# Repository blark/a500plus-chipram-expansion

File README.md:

# a500plus-chipram-expansion

This is a 1MB chip RAM expansion designed for the Amiga 500+ in KiCad.

It is in the experimental phase, but I've assembled it and it appears to be working great. However, you've been warned!

## Features

Small (42mmx52mm), simple design using only a 40 pin (2x20) female 2.54mm connector. The remaining pins are for the RTC which is on-board the A500+, so they are unecessary for RAM expansion. This makes it possible to use a 40 pin connector, which is cheaper and easier to find.

WARNING: **make sure you plug it in correctly** see the [install section](https://github.com/blark/a500plus-chipram-expansion#install) below.

## Schematic

A PDF file of the schematic can be found [in this repo](https://raw.githubusercontent.com/blark/a500plus-chipram-expansion/master/media/schematic.pdf).

## Ordering

I shared the design at [Oshpark](https://oshpark.com/shared_projects/eQQuG4Mi)

## BOM
| Designator | Description |
| ---------- | ----------- |
| J1 | 40P (20x2) female header 2.54mm |
| J2 | 1x DPDT Sub-Miniature Slide switch (9x4x3.5mm, easily found on Ebay) |
| U1-U2 | IS41C16257-35T 4mbit DRAM (256 x 16) |
| C1-C6 | 100nF 603 SMD capacitor |
| C7 | 10uF 805 SMD capacitor |
| R1 | 10K 805 SMD resistor |

## Install

Be careful during install to match pin 1 on the expansion with pin 1 on the A500+ memory expansion port! Here's an image of how it should be installed:

## Thanks

The parts library I've included (and expanded upon) in this repo is "borrowed" from [Kai Robinson](https://github.com/kr239) check out his great projects!

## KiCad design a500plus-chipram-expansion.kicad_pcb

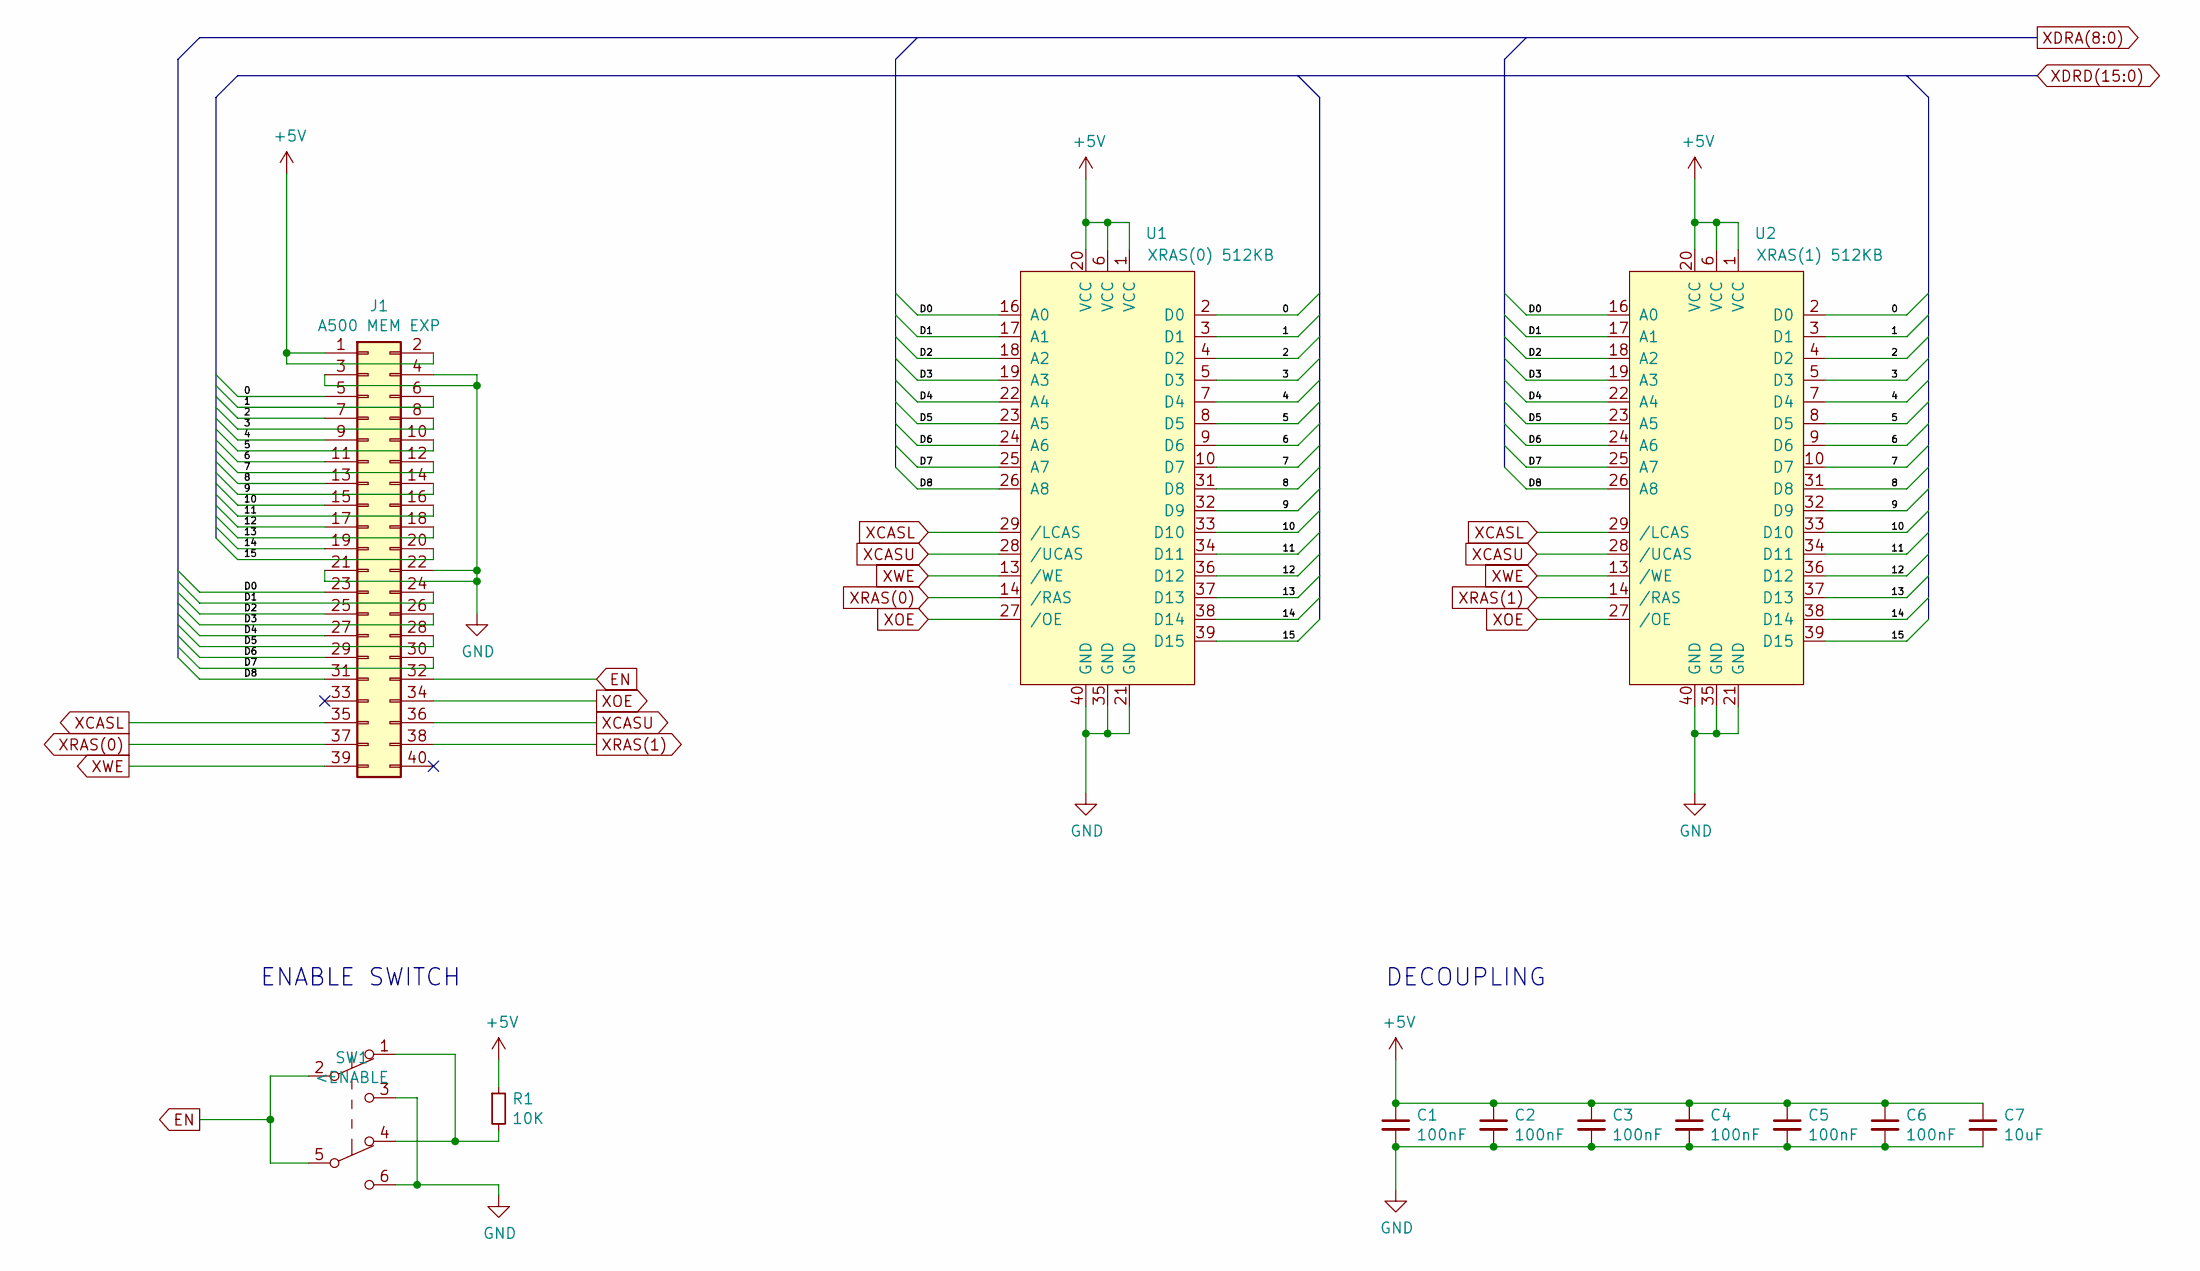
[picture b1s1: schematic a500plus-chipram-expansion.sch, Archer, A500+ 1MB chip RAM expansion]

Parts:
C1, C2, C3, C4, C5, C6: 100nF; C_0603_1608Metric_Pad1.05x0.95mm_HandSolder
C7: 10uF; C_0805_2012Metric_Pad1.15x1.40mm_HandSolder
J1: A500 MEM EXP; PinHeader_2x20_P2.54mm_Horizontal
R1: 10K; R_0805_2012Metric_Pad1.15x1.40mm_HandSolder
SW1: <ENABLE; SW_CuK_JS202011AQN_DPDT_Angled
U1: XRAS(0) 512KB; TSOP-II-40
U2: XRAS(1) 512KB; TSOP-II-40

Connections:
+5V: C1.1, C2.1, C3.1, C4.1, C5.1, C6.1, C7.1, J1.1, J1.2, R1.1, U1.1 (VCC), U1.6 (VCC), U1.20 (VCC), U2.1 (VCC), U2.6 (VCC), U2.20 (VCC)
/0: J1.5, U1.2 (D0), U2.2 (D0)
/1: J1.6, U1.3 (D1), U2.3 (D1)
/2: J1.7, U1.4 (D2), U2.4 (D2)
/3: J1.8, U1.5 (D3), U2.5 (D3)
/4: J1.9, U1.7 (D4), U2.7 (D4)
/5: J1.10, U1.8 (D5), U2.8 (D5)
/6: J1.11, U1.9 (D6), U2.9 (D6)
/7: J1.12, U1.10 (D7), U2.10 (D7)
/8: J1.13, U1.31 (D8), U2.31 (D8)
/9: J1.14, U1.32 (D9), U2.32 (D9)
/10: J1.15, U1.33 (D10), U2.33 (D10)
/11: J1.16, U1.34 (D11), U2.34 (D11)
/12: J1.17, U1.36 (D12), U2.36 (D12)
/13: J1.18, U1.37 (D13), U2.37 (D13)
/14: J1.19, U1.38 (D14), U2.38 (D14)
/15: J1.20, U1.39 (D15), U2.39 (D15)
/D0: J1.23, U1.16 (A0), U2.16 (A0)
/D1: J1.24, U1.17 (A1), U2.17 (A1)
/D2: J1.25, U1.18 (A2), U2.18 (A2)
/D3: J1.26, U1.19 (A3), U2.19 (A3)
/D4: J1.27, U1.22 (A4), U2.22 (A4)
/D5: J1.28, U1.23 (A5), U2.23 (A5)
/D6: J1.29, U1.24 (A6), U2.24 (A6)
/D7: J1.30, U1.25 (A7), U2.25 (A7)
/D8: J1.31, U1.26 (A8), U2.26 (A8)
EN: J1.32, SW1.2 (B), SW1.5 (B)
GND: C1.2, C2.2, C3.2, C4.2, C5.2, C6.2, C7.2, J1.3, J1.4, J1.21, J1.22, SW1.3 (C), SW1.6 (C), U1.21 (GND), U1.35 (GND), U1.40 (GND), U2.21 (GND), U2.35 (GND), U2.40 (GND)
unnamed: R1.2, SW1.1 (A), SW1.4 (A)
XCASL: J1.35, U1.29 (/LCAS), U2.29 (/LCAS)
XCASU: J1.36, U1.28 (/UCAS), U2.28 (/UCAS)
XOE: J1.34, U1.27 (/OE), U2.27 (/OE)
XRAS(0): J1.37, U1.14 (/RAS)
XRAS(1): J1.38, U2.14 (/RAS)
XWE: J1.39, U1.13 (/WE), U2.13 (/WE)

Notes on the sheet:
DECOUPLING
ENABLE SWITCH

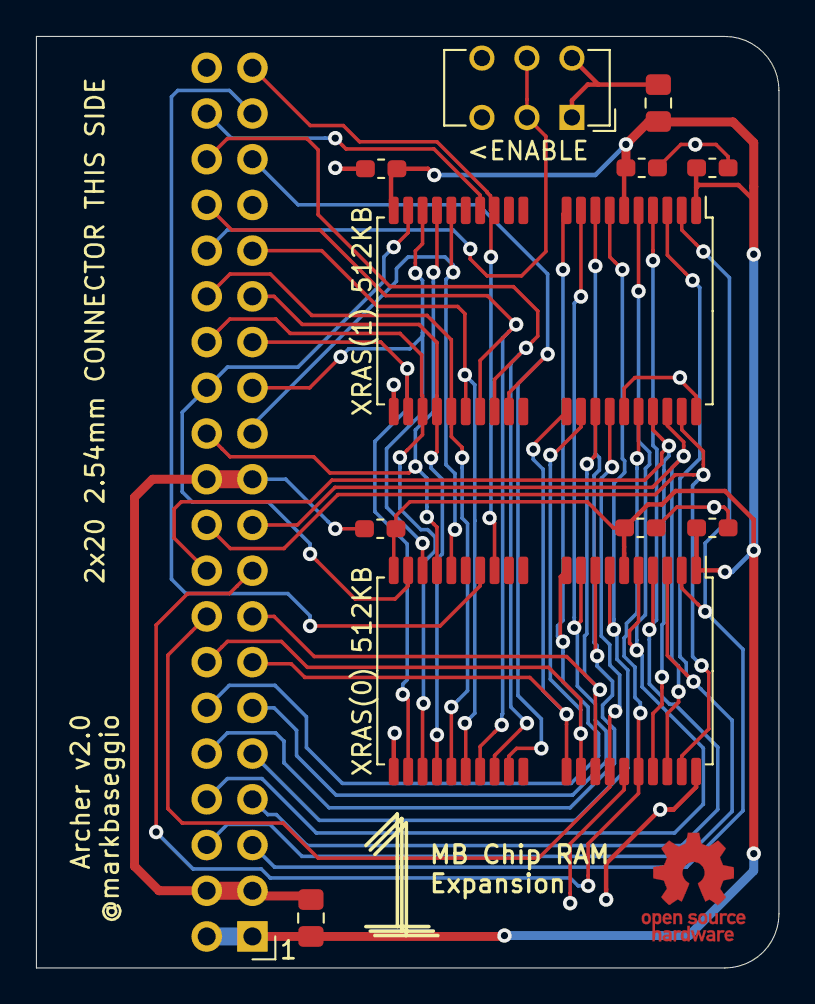
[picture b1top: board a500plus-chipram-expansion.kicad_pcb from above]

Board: 2 copper layers, 41.2 x 51.8 mm, 12 parts (0 on the bottom side), 35 nets.

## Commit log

2019-12-17 added image
2019-12-17 fix readme
2019-12-17 v1.1
2019-12-18 added install image
2019-12-18 various improvements
2020-01-07 v2.0
2020-01-07 updated image
2020-01-07 v2 gerbers first commit
2020-01-07 BOM change
2020-01-18 added oshpark link
